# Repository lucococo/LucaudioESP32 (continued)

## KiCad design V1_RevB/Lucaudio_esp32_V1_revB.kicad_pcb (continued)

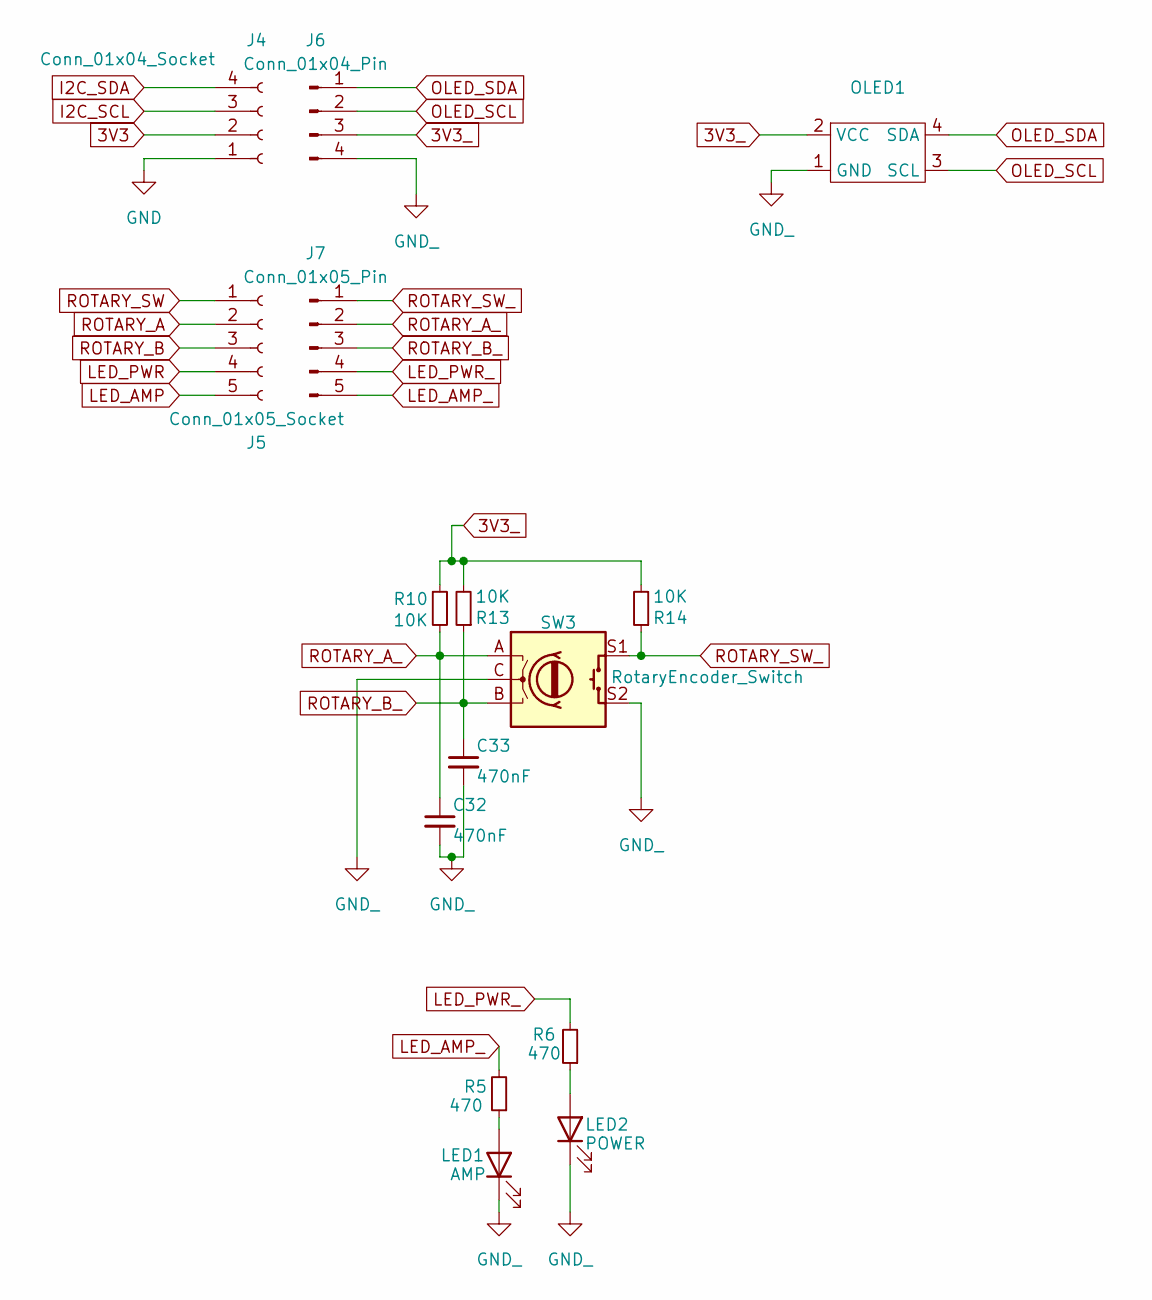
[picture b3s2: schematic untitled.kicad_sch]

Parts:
C32, C33: 470nF; C_0805_2012Metric_Pad1.18x1.45mm_HandSolder
J4: Conn_01x04_Socket; PinSocket_1x04_P2.54mm_Vertical
J5: Conn_01x05_Socket; PinSocket_1x05_P2.54mm_Vertical
J6: Conn_01x04_Pin; PinHeader_1x04_P2.54mm_Horizontal
J7: Conn_01x05_Pin; PinHeader_1x05_P2.54mm_Horizontal
LED1: AMP; LED_0805_2012Metric_Pad1.15x1.40mm_HandSolder
LED2: POWER; LED_0805_2012Metric_Pad1.15x1.40mm_HandSolder
OLED1: OLED_128_32
R5, R6: 470; R_0805_2012Metric_Pad1.20x1.40mm_HandSolder
R10, R13, R14: 10K; R_0805_2012Metric_Pad1.20x1.40mm_HandSolder
SW3: RotaryEncoder_Switch; RotaryEncoder_Alps_EC11E-Switch_Vertical_H20mm

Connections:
3V3: J4.2; also elsewhere on the board
3V3_: J6.3, OLED1.2 (VCC), R10.1, R13.2, R14.2
GND: J4.1; also elsewhere on the board
GND_: C32.2, C33.2, J6.4, LED1.1 (K), LED2.1 (K), OLED1.1 (GND), SW3.C, SW3.S2
GPIO12: J5.5; also elsewhere on the board
GPIO13: J5.4; also elsewhere on the board
I2C_SCL: J4.3; also elsewhere on the board
I2C_SDA: J4.4; also elsewhere on the board
LED_AMP_: J7.5, R5.2
LED_PWR_: J7.4, R6.2
unnamed: LED1.2 (A), R5.1
unnamed: LED2.2 (A), R6.1
OLED_SCL: J6.2, OLED1.3 (SCL)
OLED_SDA: J6.1, OLED1.4 (SDA)
ROTARY_A: J5.2; also elsewhere on the board
ROTARY_A_: C32.1, J7.2, R10.2, SW3.A
ROTARY_B: J5.3; also elsewhere on the board
ROTARY_B_: C33.1, J7.3, R13.1, SW3.B
ROTARY_SW: J5.1; also elsewhere on the board
ROTARY_SW_: J7.1, R14.1, SW3.S1

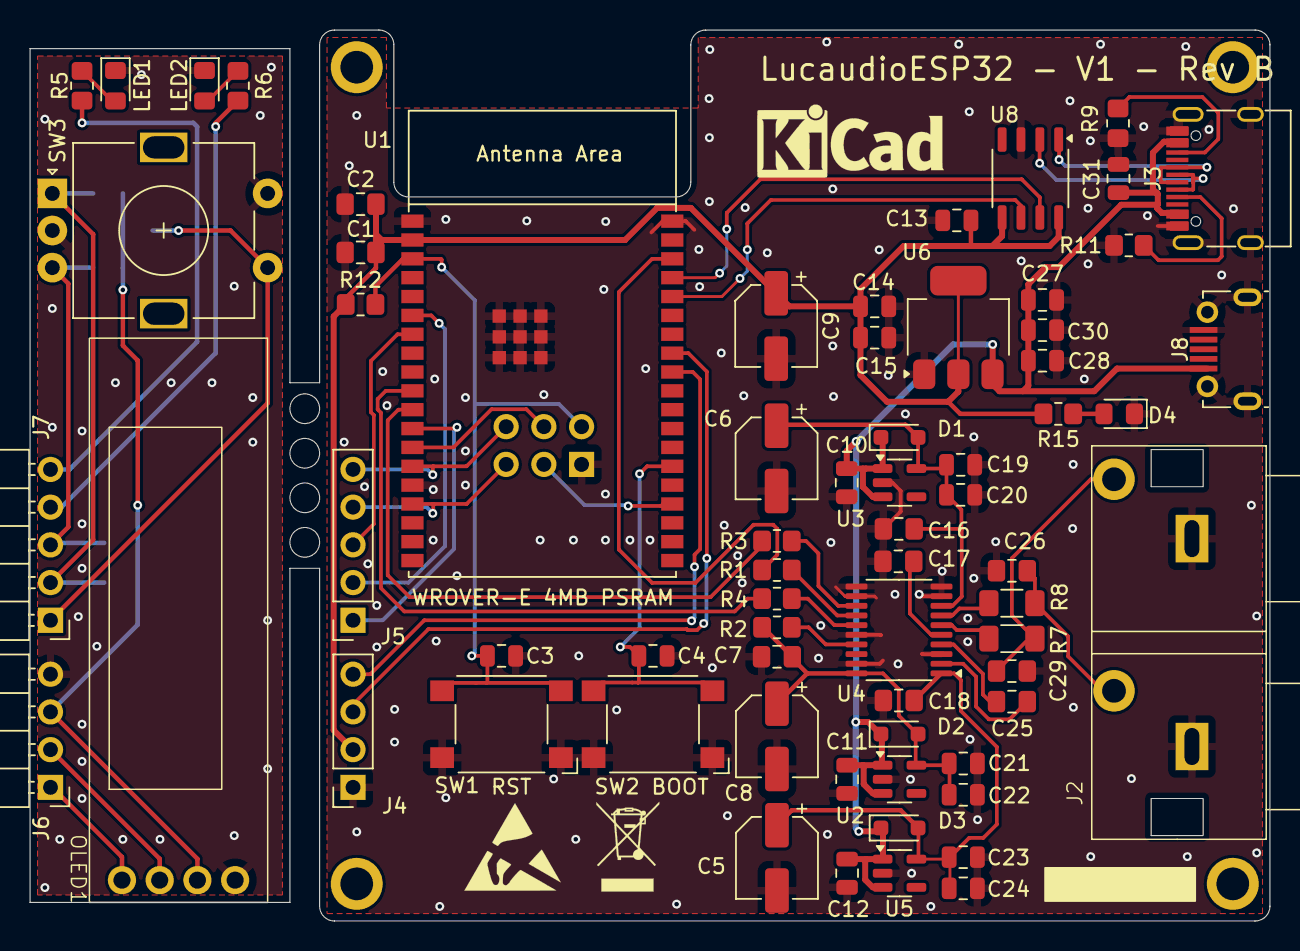
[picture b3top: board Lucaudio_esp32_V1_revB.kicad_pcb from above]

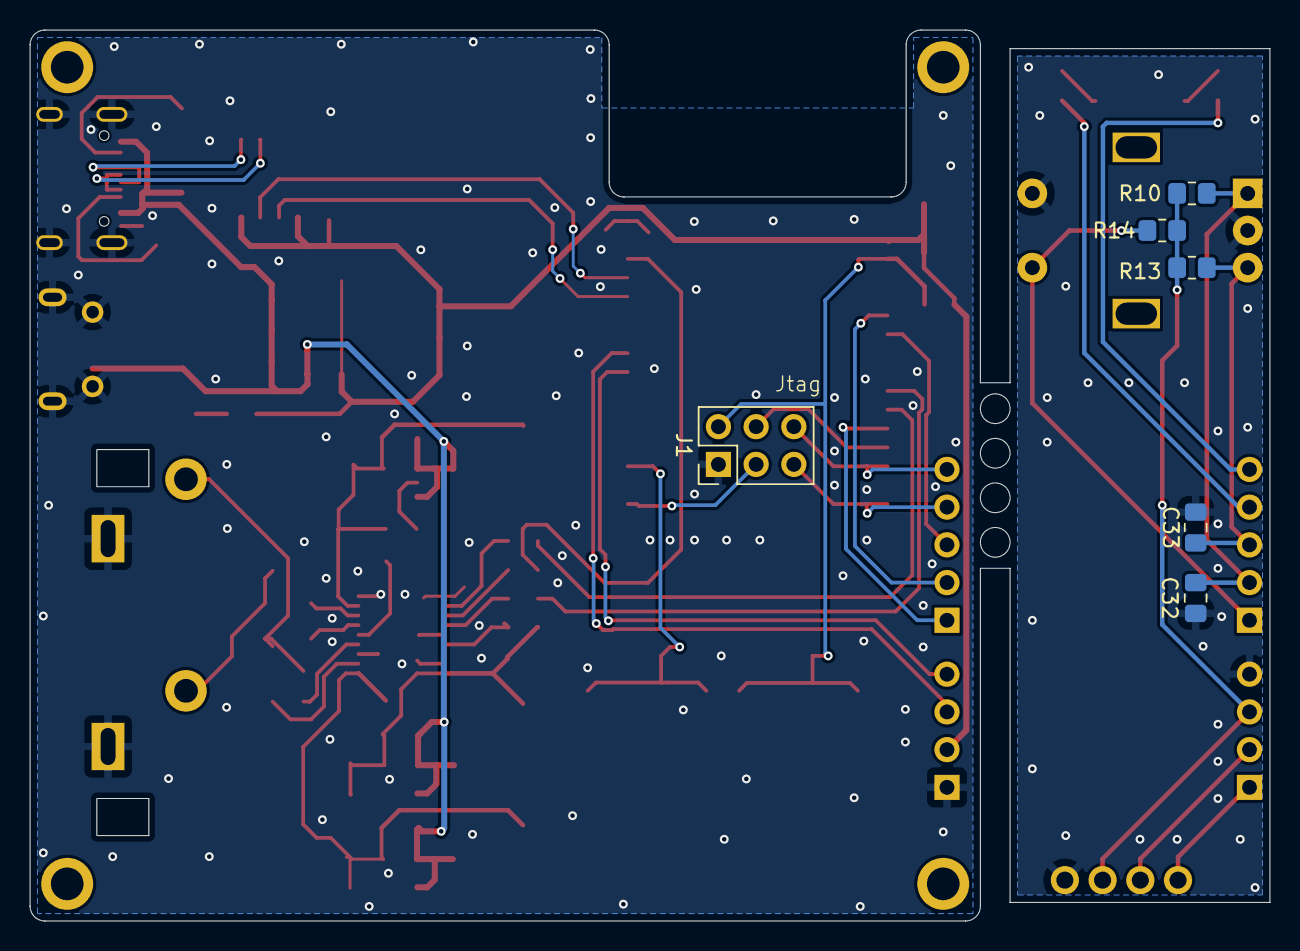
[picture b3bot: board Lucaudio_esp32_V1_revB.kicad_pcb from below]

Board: 2 copper layers, 83.5 x 60.0 mm, 73 parts (6 on the bottom side), 49 nets.

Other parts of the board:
C31: 100nF; C_0805_2012Metric

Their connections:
+5V: C31.1; also elsewhere on the board
GND: C31.2; also elsewhere on the board

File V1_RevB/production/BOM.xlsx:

Designator | Footprint | Quantity | Value | LCSC Part #
C1 | 0805 | 1 | 4.7uF | C6119943
C10, C11, C12, C20, C22, C24 | 0805 | 6 | 1uF | C376929
C13, C15, C16, C18, C19, C2, C21, C23, C28, C3, C30, C31, C4, C7 | 0805 | 14 | 100nF | C476766
C14, C27 | 0805 | 2 | 10uF | C6119932
C17, C25 | 0805 | 2 | 2.2uF | C7432779
C26, C29 | 0805 | 2 | 2.2nF | C5254797
C32, C33 | 0805 | 2 | 470nF | C2859120
C5, C6, C8, C9 | CP_Elec_5x4.5 | 4 | 10uF | C20607178
D1, D2, D3 | D_SOD-323_HandSoldering | 3 | 1N5819WS | C191023
D4 | 0805 | 1 | LED | C965812
J1 | PinHeader_2x03_P2.54mm_Vertical | 1 | jtag
J2 | 2x RCA | 1 | Conn_Coaxial_x2
J3 | USB_C_Receptacle_G-Switch_GT-USB-7010ASV | 1 | USB_C_Receptacle_USB2.0_16P | C7506788
J4 | PinSocket_1x04_P2.54mm_Vertical | 1 | Conn_01x04_Socket
J5 | PinSocket_1x05_P2.54mm_Vertical | 1 | Conn_01x05_Socket
J6 | PinHeader_1x04_P2.54mm_Horizontal | 1 | Conn_01x04_Pin
J7 | PinHeader_1x05_P2.54mm_Horizontal | 1 | Conn_01x05_Pin
J8 | USB_Micro-B_Molex-105017-0001 | 1 | USB_B_Micro | C404969
LED1 | 0805 | 1 | AMP | C965812
LED2 | 0805 | 1 | POWER | C688885
OLED1 | OLED_128_32 | 1 | ~ | C5248081
R1, R15, R2, R3, R4, R5, R6 | 0805 | 7 | 470 | C21571494
R10, R12, R13, R14 | 0805 | 4 | 10K | C17414
R11, R9 | 0805 | 2 | 5.1k | C26023
R7, R8 | 1206 | 2 | 470 | C4502
SW1, SW2 | SW_SPST_Omron_B3FS-100xP | 2 | SW_Omron_B3FS | C87038
SW3 | RotaryEncoder_Alps_EC11E-Switch_Vertical_H20mm | 1 | RotaryEncoder_Switch | C470742
U1 | ESP32-WROVER-E | 1 | ESP32-WROVER-E | C2973667
U2, U3, U5 | SOT-23-5 | 3 | LP5907MFX-3.3 | C80670
U4 | TSSOP-20_4.4x6.5mm_P0.65mm | 1 | PCM5100 | C131154
U6 | SOT-223-3_TabPin2 | 1 | TLV1117-33 | C37359
U8 | SOP-8_3.9x4.9mm_P1.27mm | 1 | CH340N | C2977777

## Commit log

2024-07-24 Initial commit of KiCad project
2024-07-24 arranging files
2024-10-22 new version including external screen, rotary encoder for volume control and power leds
2024-10-22 Update README.md
    RevC upload
2024-11-13 adding V1.1.0
2024-12-11 Revamping folders
2024-12-11 Add nvs parameters json
2024-12-16 Backlink to CADLAB.io has been added.
2024-12-16 Added I2C screen, rotary encoder and led status
2025-11-18 Revamping folders and added 2.0 and 2.1 on git
